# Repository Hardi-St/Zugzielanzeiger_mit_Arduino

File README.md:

# Zugzielanzeiger_mit_Arduino
Zugzielanzeiger für den Bahnsteig mit Arduino und OLED Display

Siehe: https://www.stummiforum.de/viewtopic.php?f=21&t=131472

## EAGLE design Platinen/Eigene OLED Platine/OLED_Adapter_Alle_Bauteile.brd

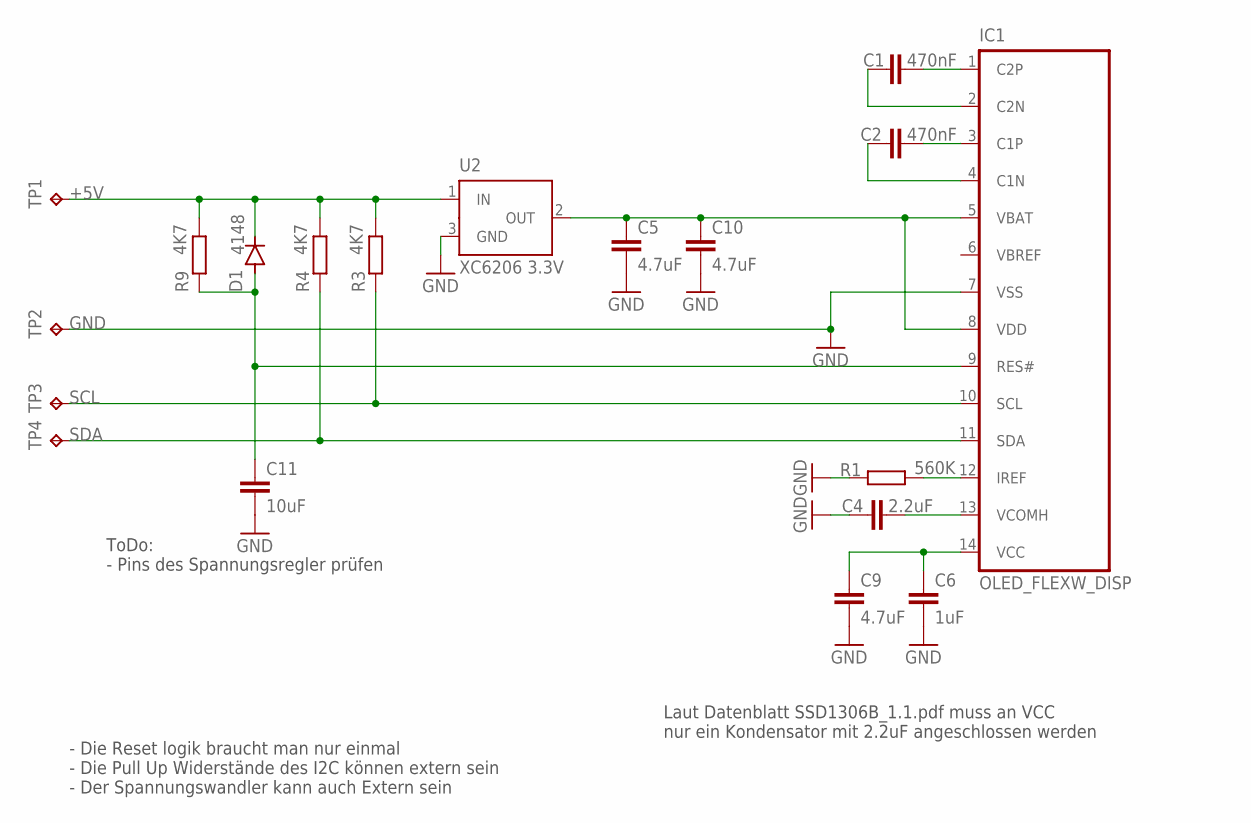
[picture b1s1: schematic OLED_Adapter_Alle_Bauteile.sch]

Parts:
C1, C2: 470nF; C0603
C4: 2.2uF; C0603
C5, C9, C10: 4.7uF; C0603
C6: 1uF; C0603
C11: 10uF; C0603
D1: 4148; SOD-123_MINI-SMA
IC1: OLED_FLEXW_DISP; OLED_FLEX_W_DISP
R1: 560K; R0603
R3, R4, R9: 4K7; R0603
TP1: TPTP10SQ; TP10SQ
TP2, TP3, TP4: TPTP10R; TP10R
U2: XC6206 3.3V; SOT23

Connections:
+5V: D1.C, R3.2, R4.2, R9.2, TP1.TP, U2.1 (IN)
GND: C4.1, C5.2, C6.2, C9.2, C10.2, C11.2, IC1.7 (VSS), R1.1, TP2.TP, U2.3 (GND)
unnamed: IC1.12 (IREF), R1.2
unnamed: C5.1, C10.1, IC1.5 (VBAT), IC1.8 (VDD), U2.2 (OUT)
unnamed: C1.2, IC1.1 (C2P)
unnamed: C1.1, IC1.2 (C2N)
unnamed: C2.2, IC1.3 (C1P)
unnamed: C2.1, IC1.4 (C1N)
unnamed: C6.1, C9.1, IC1.14 (VCC)
unnamed: C4.2, IC1.13 (VCOMH)
unnamed: C11.1, D1.A, IC1.9 (RES#), R9.1
SCL: IC1.10 (SCL), R3.1, TP3.TP
SDA: IC1.11 (SDA), R4.1, TP4.TP

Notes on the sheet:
ToDo: - Pins des Spannungsregler prüfen
Laut Datenblatt SSD1306B_1.1.pdf muss an VCC nur ein Kondensator mit 2.2uF angeschlossen werden
- Die Reset logik braucht man nur einmal - Die Pull Up Widerstände des I2C können extern sein - Der Spannungswandler kann auch Extern sein

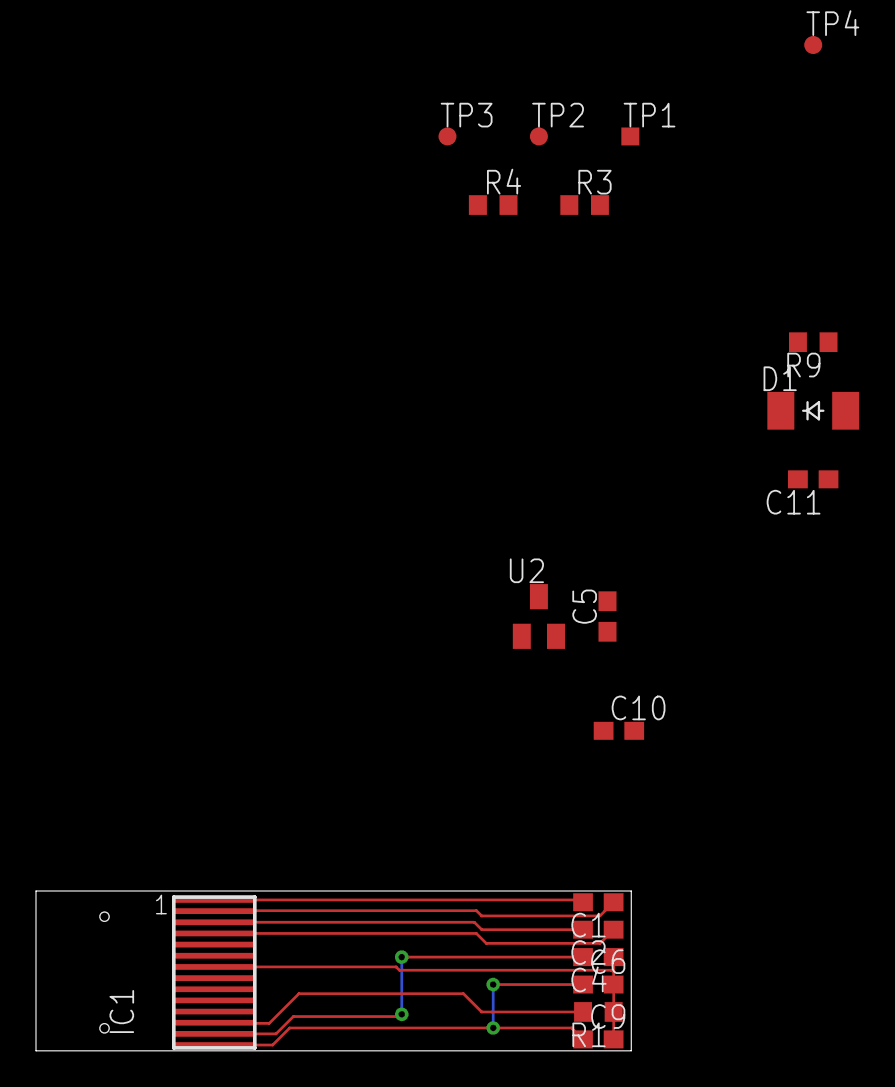
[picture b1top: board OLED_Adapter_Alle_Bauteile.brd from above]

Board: 2 copper layers, 33.1 x 8.9 mm, 19 parts (0 on the bottom side), 13 nets.

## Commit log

2020-10-03 Initial upload
2020-10-03 Anleitungen hinzugefuegt
    + 760DE_Bahnsteigs-Anzeige-OLED_mit_1x_Display.pdf
    + 760DE_Bahnsteigs-Anzeige-OLED_mit_2x_Display.pdf
2020-10-04 Gehaeuse-Zugzielanzeiger-0.87"
2020-11-07 Korrektur Werte der Bauteile in der Beschreibung.
2021-03-28 Update Stuecklisten
